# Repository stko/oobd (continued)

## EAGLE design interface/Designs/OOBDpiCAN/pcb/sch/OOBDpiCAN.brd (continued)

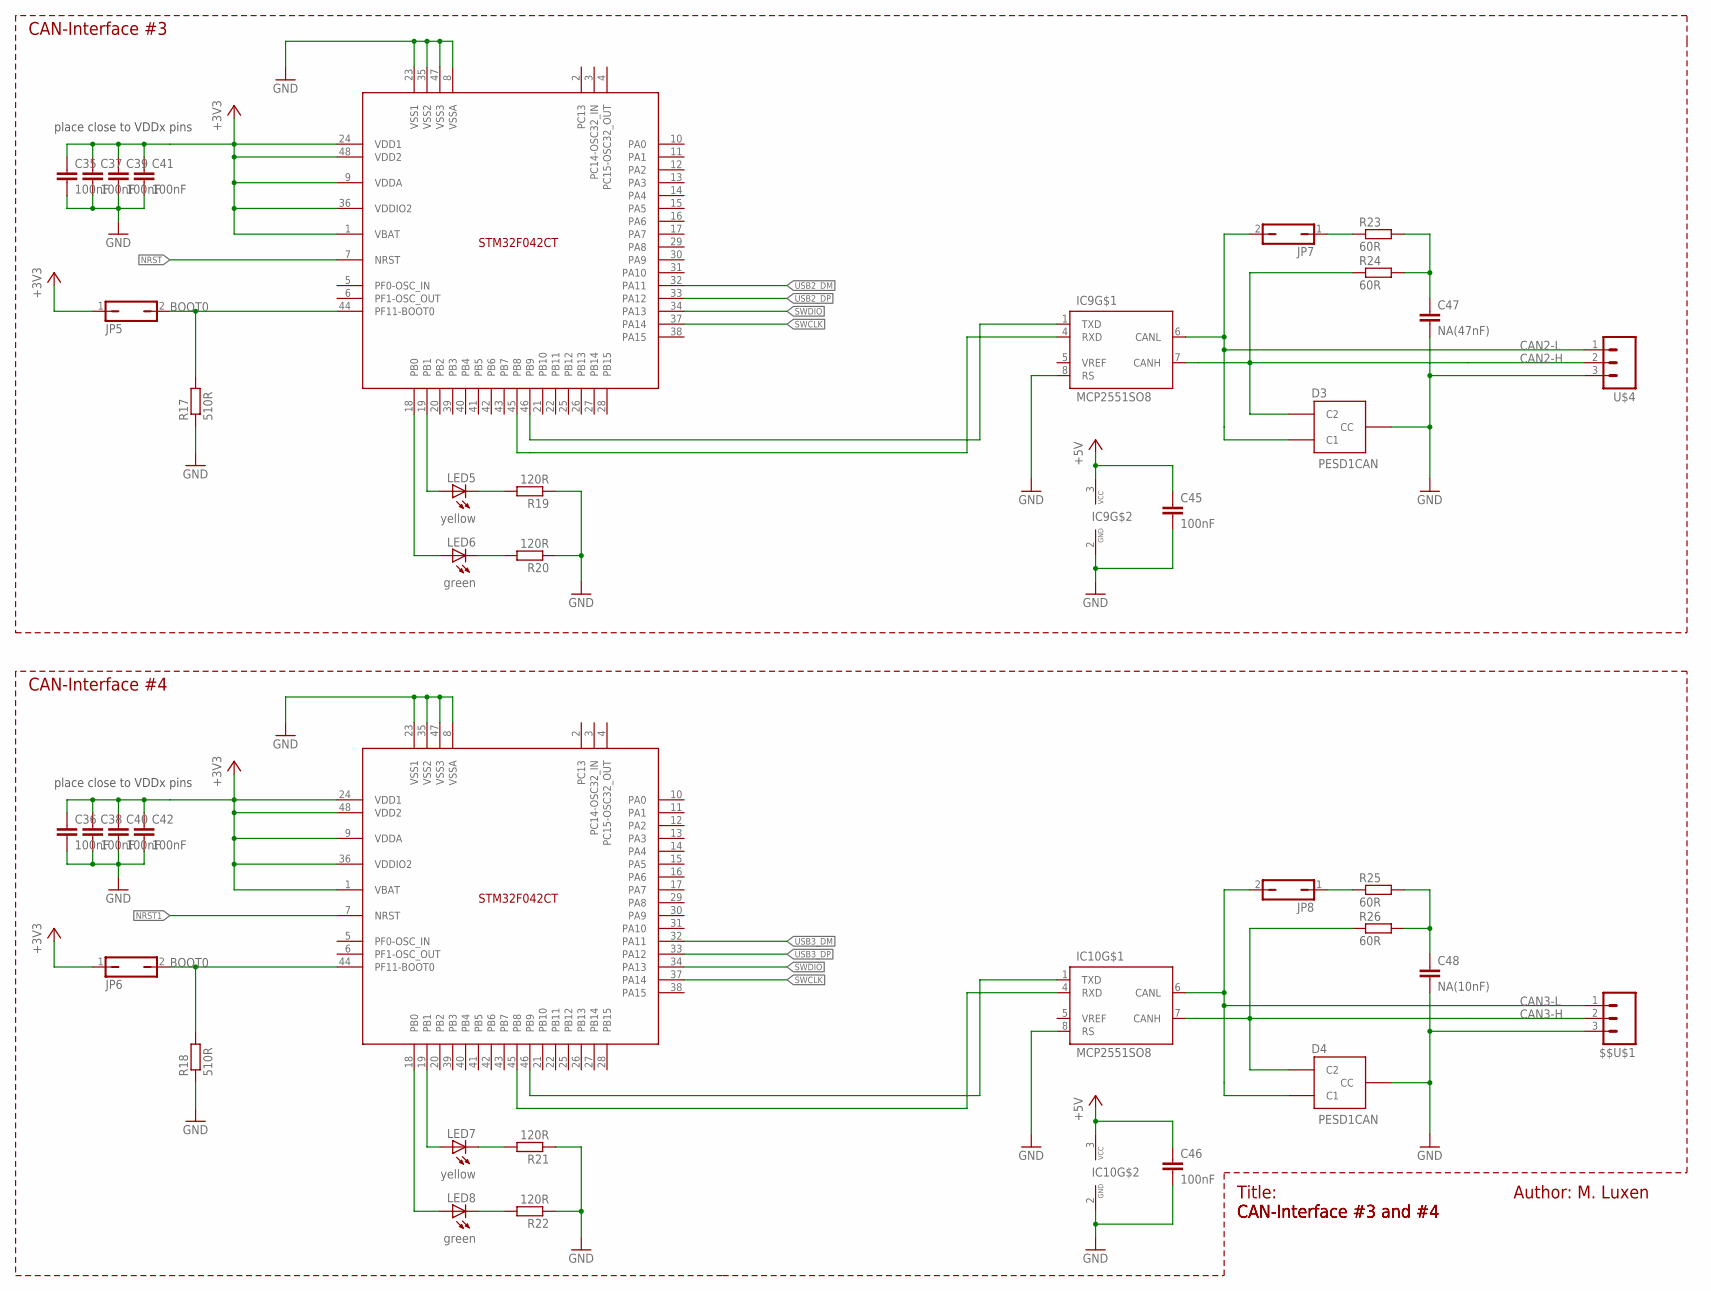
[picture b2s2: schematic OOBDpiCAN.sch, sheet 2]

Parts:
$$U$1: M03; SCREWTERMINAL-3.5MM-3
C35, C36, C37, C38, C39, C40, C41, C42, C45, C46: 100nF; C0603
C47: NA(47nF); C0603
C48: NA(10nF); C0603
D3, D4: PESD1CAN; SOT23
IC7, IC8: STM32F042CT; LQFP48
IC9, IC10: MCP2551SO8; SO08
JP5, JP6, JP7, JP8: JP1Q; JP1
LED5, LED7: yellow; CHIPLED_0805
LED6, LED8: green; CHIPLED_0805
R17, R18: 510R; R0603
R19, R20, R21, R22: 120R; R0603
R23, R24, R25, R26: 60R; R0603
U$4: M03; SCREWTERMINAL-3.5MM-3

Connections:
+3V3: C35.1, C36.1, C37.1, C38.1, C39.1, C40.1, C41.1, C42.1, IC7.1 (VBAT), IC7.9 (VDDA), IC7.24 (VDD1), IC7.36 (VDDIO2), IC7.48 (VDD2), IC8.1 (VBAT), IC8.9 (VDDA), IC8.24 (VDD1), IC8.36 (VDDIO2), IC8.48 (VDD2), JP5.1, JP6.1; also elsewhere on the board
+5V: C45.1, C46.1, IC9.3 (VCC), IC10.3 (VCC); also elsewhere on the board
BOOT0: IC7.44 (PF11-BOOT0), IC8.44 (PF11-BOOT0), JP5.2, JP6.2, R17.2, R18.2; also elsewhere on the board
CAN2-H: D3.2 (C2), IC9.7 (CANH), R24.1, U$4.2 (3)
CAN2-L: D3.1 (C1), IC9.6 (CANL), JP7.2, U$4.1 (2)
CAN3-H: $$U$1.2 (3), D4.2 (C2), IC10.7 (CANH), R26.1
CAN3-L: $$U$1.1 (2), D4.1 (C1), IC10.6 (CANL), JP8.2
GND: $$U$1.3 (4), C35.2, C36.2, C37.2, C38.2, C39.2, C40.2, C41.2, C42.2, C45.2, C46.2, C47.2, C48.2, D3.3 (CC), D4.3 (CC), IC7.8 (VSSA), IC7.23 (VSS1), IC7.35 (VSS2), IC7.47 (VSS3), IC8.8 (VSSA), IC8.23 (VSS1), IC8.35 (VSS2), IC8.47 (VSS3), IC9.2 (GND), IC9.8 (RS), IC10.2 (GND), IC10.8 (RS), R17.1, R18.1, R19.1, R20.1, R21.1, R22.1, U$4.3 (4); also elsewhere on the board
unnamed: IC7.19 (PB1), LED5.A
unnamed: JP7.1, R23.1
unnamed: IC7.18 (PB0), LED6.A
unnamed: LED5.C, R19.2
unnamed: LED6.C, R20.2
unnamed: IC8.19 (PB1), LED7.A
unnamed: IC8.18 (PB0), LED8.A
unnamed: LED7.C, R21.2
unnamed: LED8.C, R22.2
unnamed: C47.1, R23.2, R24.2
unnamed: IC8.45 (PB8), IC10.4 (RXD)
unnamed: IC8.46 (PB9), IC10.1 (TXD)
unnamed: IC7.45 (PB8), IC9.4 (RXD)
unnamed: IC7.46 (PB9), IC9.1 (TXD)
unnamed: JP8.1, R25.1
unnamed: C48.1, R25.2, R26.2
NRST: IC7.7 (NRST); also elsewhere on the board
NRST1: IC8.7 (NRST)
SWCLK: IC7.37 (PA14), IC8.37 (PA14); also elsewhere on the board
SWDIO: IC7.34 (PA13), IC8.34 (PA13); also elsewhere on the board
USB2_DM: IC7.32 (PA11); also elsewhere on the board
USB2_DP: IC7.33 (PA12); also elsewhere on the board
USB3_DM: IC8.32 (PA11); also elsewhere on the board
USB3_DP: IC8.33 (PA12); also elsewhere on the board

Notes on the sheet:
place close to VDDx pins
Author: M. Luxen
Title:
CAN-Interface #3 and #4
CAN-Interface #4
CAN-Interface #3

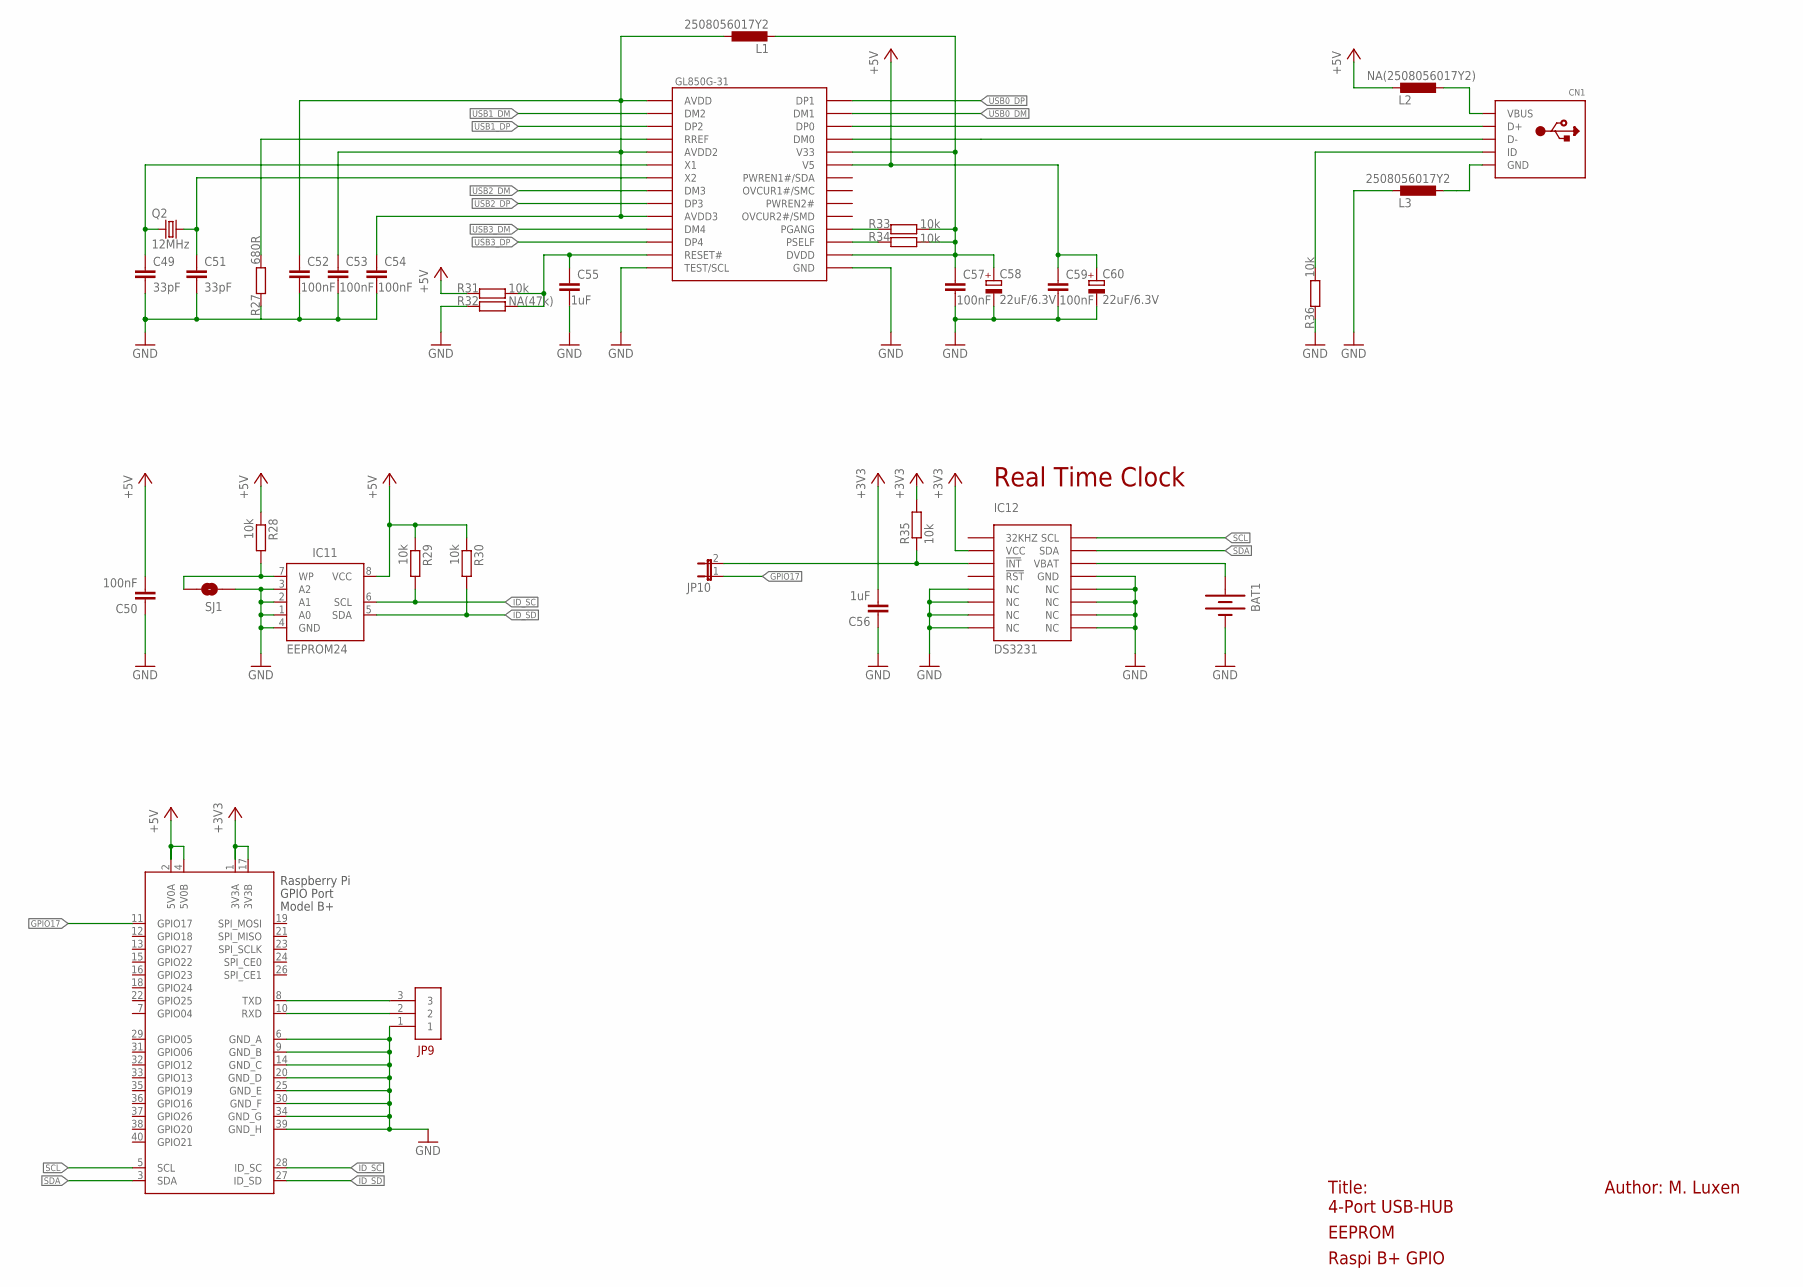
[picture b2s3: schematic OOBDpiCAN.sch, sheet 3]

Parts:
BAT1: BATTERY12PTH; BATTCON_12MM_PTH
C49, C51: 33pF; C0603
C50, C52, C53, C54, C57, C59: 100nF; C0603
C55, C56: 1uF; C0603
C58, C60: 22uF/6.3V; SMC_A
CN1: USBMOLEX; USB-MINIB-THM-MOLEX
IC11: EEPROM24; SOIC8
IC12: DS3231; SOIC-16W
JP9: MA03-1
JP10: JUMPER-2SMD-NO; SJ_2S-NO
L1, L3: 2508056017Y2; L0805
L2: NA(2508056017Y2); L0805
Q2: 12MHz; SM49
R27: 680R; R0603
R28, R29, R30, R31, R33, R34, R35, R36: 10k; R0603
R32: NA(47k); R0603
RPI1: RASPBERRY_HATHAT; CONNECTOR_B+_SMT_HAT
SJ1: SOLDERJUMPERTRACE; SJ_2S-TRACE
U$5: GL850G-31; TSSOP28

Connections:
+3V3: C56.2, IC12.2 (VCC), R35.2, RPI1.1 (3V3A), RPI1.17 (3V3B); also elsewhere on the board
+5V: C50.2, C59.1, C60.+, IC11.8 (VCC), L2.1, R28.1, R29.1, R30.1, R31.1, RPI1.2 (5V0A), RPI1.4 (5V0B), U$5.23 (V5); also elsewhere on the board
GND: BAT1.GND (-), C49.2, C50.1, C51.2, C52.2, C53.2, C54.2, C55.2, C56.1, C57.2, C58.-, C59.2, C60.-, IC11.1 (A0), IC11.2 (A1), IC11.3 (A2), IC11.4 (GND), IC12.5 (NC), IC12.6 (NC), IC12.7 (NC), IC12.8 (NC), IC12.9 (NC), IC12.10 (NC), IC12.11 (NC), IC12.12 (NC), IC12.13 (GND), JP9.1, L3.1, R27.1, R32.1, R36.1, RPI1.6 (GND_A), RPI1.9 (GND_B), RPI1.14 (GND_C), RPI1.20 (GND_D), RPI1.25 (GND_E), RPI1.30 (GND_F), RPI1.34 (GND_G), RPI1.39 (GND_H), SJ1.1, U$5.14 (TEST/SCL), U$5.15 (GND); also elsewhere on the board
GPIO17: JP10.1, RPI1.11 (GPIO17)
ID_SC: IC11.6 (SCL), R29.2, RPI1.28 (ID_SC)
ID_SD: IC11.5 (SDA), R30.2, RPI1.27 (ID_SD)
INT-: IC12.3 (!INT), JP10.2, R35.1
unnamed: C51.1, Q2.2, U$5.7 (X2)
unnamed: C49.1, Q2.1, U$5.6 (X1)
unnamed: IC11.7 (WP), R28.2, SJ1.2
unnamed: C57.1, C58.+, L1.2, R33.2, R34.2, U$5.16 (DVDD), U$5.24 (V33)
unnamed: R33.1, U$5.18 (PGANG)
unnamed: R34.1, U$5.17 (PSELF)
unnamed: C55.1, R31.2, R32.2, U$5.13 (RESET#)
unnamed: CN1.D+, U$5.26 (DP0)
unnamed: CN1.D-, U$5.25 (DM0)
unnamed: C52.1, C53.1, C54.1, L1.1, U$5.1 (AVDD), U$5.5 (AVDD2), U$5.10 (AVDD3)
unnamed: R27.2, U$5.4 (RREF)
unnamed: CN1.GND, L3.2
unnamed: CN1.VBUS, L2.2
unnamed: CN1.ID, R36.2
RXD: JP9.2, RPI1.10 (RXD)
SCL: IC12.16 (SCL), RPI1.5 (SCL)
SDA: IC12.15 (SDA), RPI1.3 (SDA)
TXD: JP9.3, RPI1.8 (TXD)
USB0_DM: U$5.27 (DM1); also elsewhere on the board
USB0_DP: U$5.28 (DP1); also elsewhere on the board
USB1_DM: U$5.2 (DM2); also elsewhere on the board
USB1_DP: U$5.3 (DP2); also elsewhere on the board
USB2_DM: U$5.8 (DM3); also elsewhere on the board
USB2_DP: U$5.9 (DP3); also elsewhere on the board
USB3_DM: U$5.11 (DM4); also elsewhere on the board
USB3_DP: U$5.12 (DP4); also elsewhere on the board
VBAT: BAT1.VCC@1 (+), IC12.14 (VBAT)

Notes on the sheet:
Author: M. Luxen
Title:
4-Port USB-HUB
Real Time Clock
EEPROM
Raspi B+ GPIO

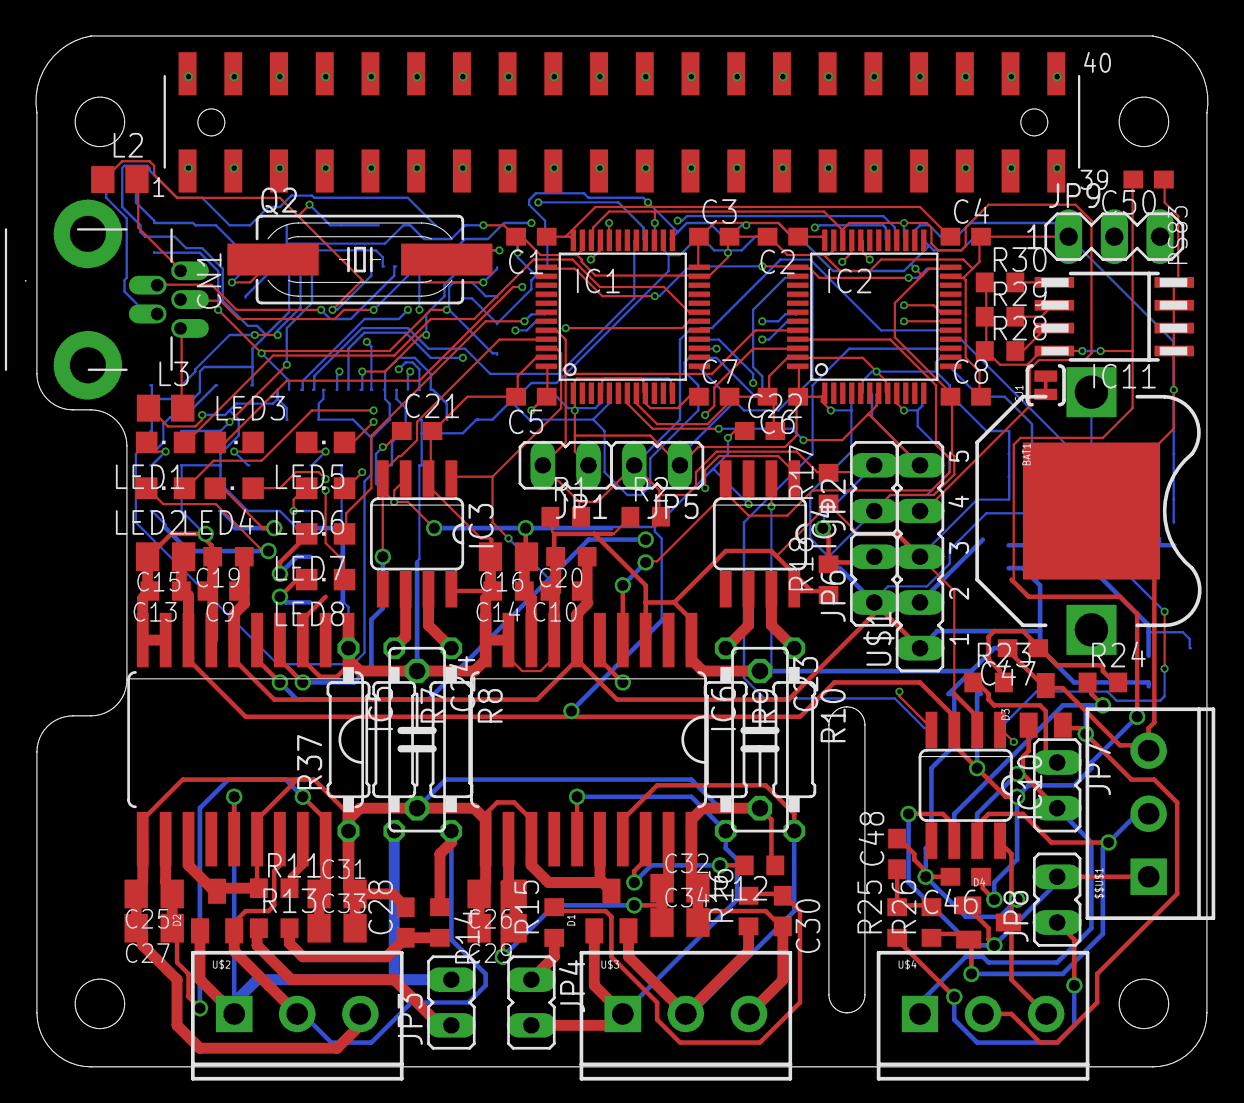
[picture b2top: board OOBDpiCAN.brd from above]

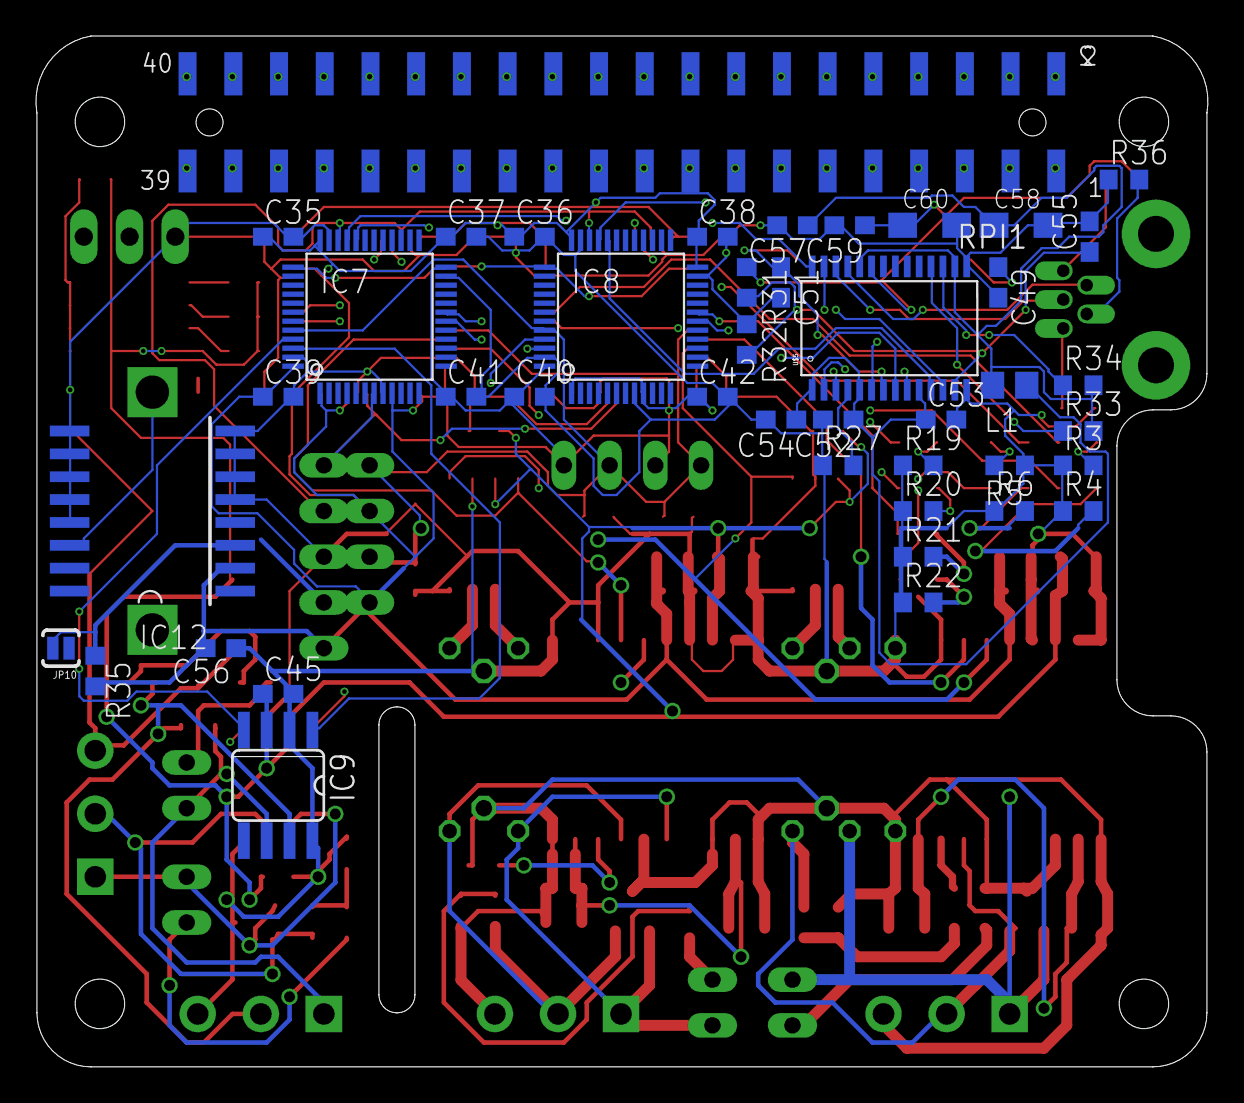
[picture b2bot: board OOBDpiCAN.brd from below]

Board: 4 copper layers, 65.1 x 57.3 mm, 139 parts (42 on the bottom side), 87 nets.

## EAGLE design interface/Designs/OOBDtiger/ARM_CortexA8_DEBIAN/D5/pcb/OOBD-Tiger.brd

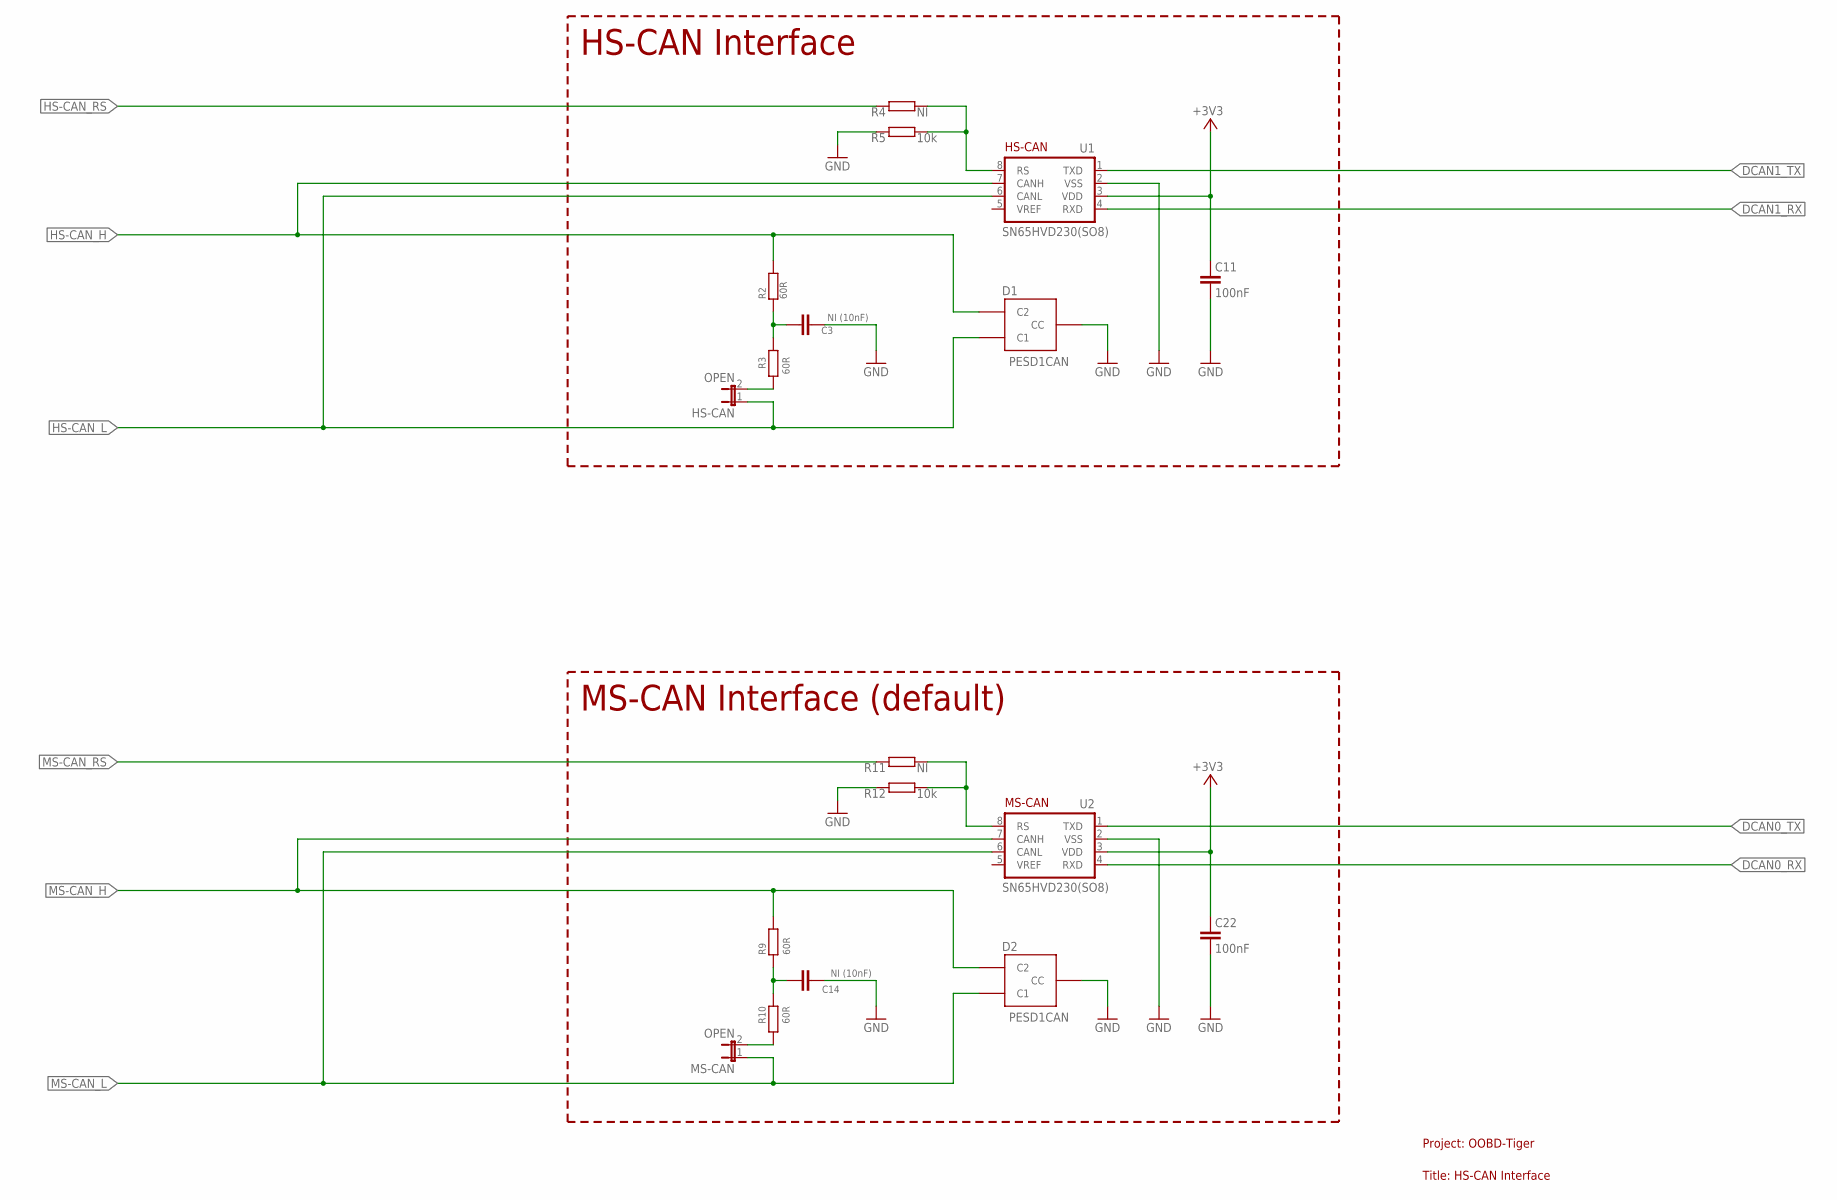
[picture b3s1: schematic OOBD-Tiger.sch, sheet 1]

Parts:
C3, C14: NI (10nF); C0603
C11, C22: 100nF; C0603K
D1, D2: PESD1CAN; SOT23
HS-CAN: OPEN; 1X02
MS-CAN: OPEN; 1X02
R2, R3, R9, R10: 60R; R0603
R4, R11: NI; R0603
R5, R12: 10k; R0603
U1, U2: SN65HVD230(SO8); SO-08

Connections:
DCAN0_RX: U2.4 (RXD); also elsewhere on the board
DCAN0_TX: U2.1 (TXD); also elsewhere on the board
DCAN1_RX: U1.4 (RXD); also elsewhere on the board
DCAN1_TX: U1.1 (TXD); also elsewhere on the board
GND: C3.2, C11.2, C14.2, C22.2, D1.3 (CC), D2.3 (CC), R5.2, R12.2, U1.2 (VSS), U2.2 (VSS); also elsewhere on the board
HS-CAN_H: D1.2 (C2), R2.2, U1.7 (CANH); also elsewhere on the board
HS-CAN_L: D1.1 (C1), HS-CAN.1, U1.6 (CANL); also elsewhere on the board
HS-CAN_RS: R4.2; also elsewhere on the board
MS-CAN_H: D2.2 (C2), R9.2, U2.7 (CANH); also elsewhere on the board
MS-CAN_L: D2.1 (C1), MS-CAN.1, U2.6 (CANL); also elsewhere on the board
MS-CAN_RS: R11.2; also elsewhere on the board
unnamed: C3.1, R2.1, R3.1
unnamed: R4.1, R5.1, U1.8 (RS)
unnamed: C14.1, R9.1, R10.1
unnamed: HS-CAN.2, R3.2
unnamed: MS-CAN.2, R10.2
unnamed: R11.1, R12.1, U2.8 (RS)

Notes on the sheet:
HS-CAN Interface
Project: OOBD-Tiger
Title: HS-CAN Interface
HS-CAN
MS-CAN Interface (default)
MS-CAN

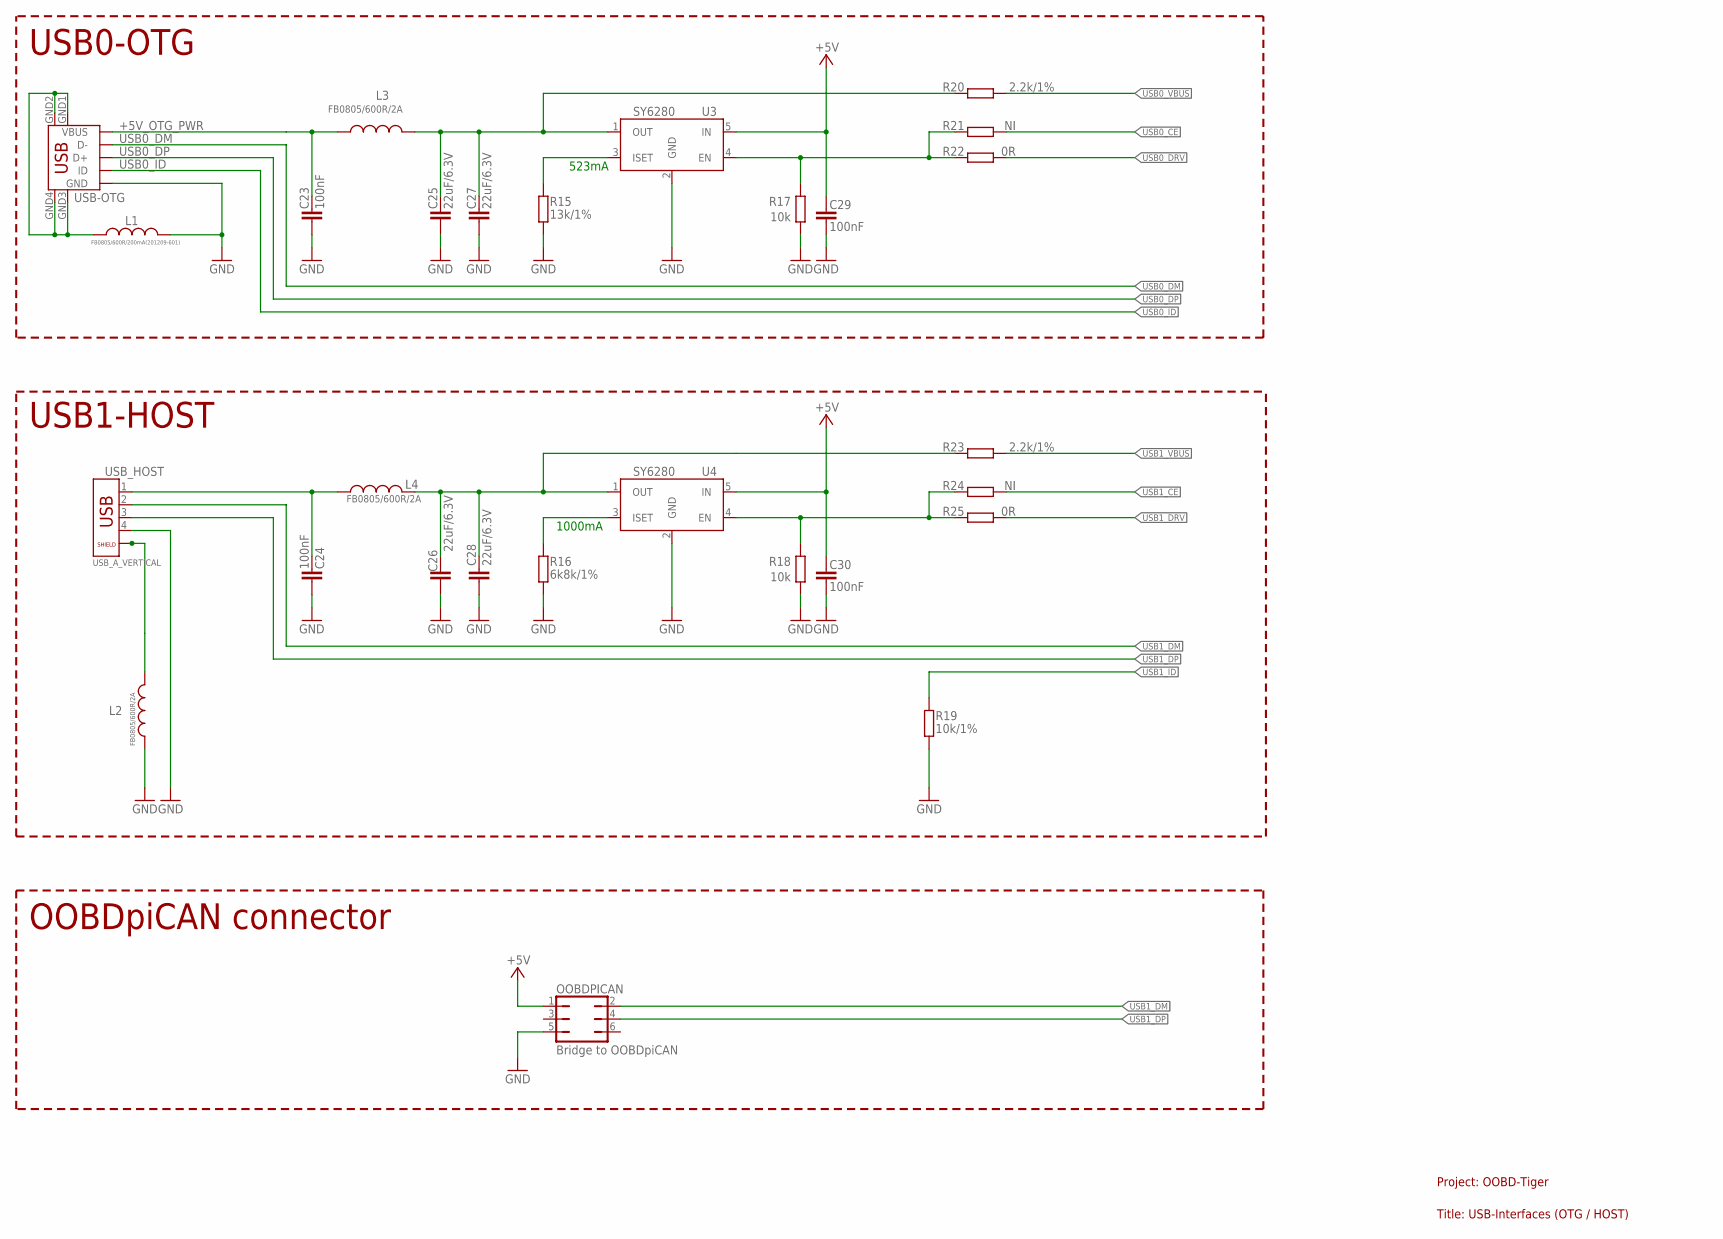
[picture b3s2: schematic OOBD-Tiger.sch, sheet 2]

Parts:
C23, C24, C29, C30: 100nF; C0603K
C25, C26, C27, C28: 22uF/6.3V; C0603
L1: FB0805/600R/200mA(201209-601); L0603
L2, L3, L4: FB0805/600R/2A; L0603
OOBDPICAN: Bridge to OOBDpiCAN; JP3Q
R15: 13k/1%; R0603
R16: 6k8k/1%; R0603
R17, R18: 10k; R0603
R19: 10k/1%; R0603
R20, R23: 2.2k/1%; R0603
R21, R24: NI; R0603
R22, R25: 0R; R0603
U3, U4: SY6280; SOT23-5
USB_HOST: USB_A_VERTICAL; USB_PN87520_DEV_PTH
USB_OTG: USB-OTG; USB_MINI_9PIN

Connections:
+5V: C29.1, C30.1, OOBDPICAN.1, U3.5 (IN), U4.5 (IN); also elsewhere on the board
+5V_OTG_PWR: C23.1, L3.1, USB_OTG.VBUS
GND: C23.2, C24.2, C25.2, C26.2, C27.2, C28.2, C29.2, C30.2, L1.1, L2.1, OOBDPICAN.5, R15.1, R16.1, R17.1, R18.1, R19.1, U3.2 (GND), U4.2 (GND), USB_HOST.4, USB_OTG.GND; also elsewhere on the board
unnamed: R16.2, U4.3 (ISET)
unnamed: C26.1, C28.1, L4.1, R23.2, U4.1 (OUT)
unnamed: C24.1, L4.2, USB_HOST.1
unnamed: L2.2, USB_HOST.P$1 (5), USB_HOST.P$2 (6)
unnamed: R15.2, U3.3 (ISET)
unnamed: C25.1, C27.1, L3.2, R20.2, U3.1 (OUT)
unnamed: L1.2, USB_OTG.GND1, USB_OTG.GND2, USB_OTG.GND3, USB_OTG.GND4
USB0_CE: R21.2; also elsewhere on the board
USB0_DM: USB_OTG.D-; also elsewhere on the board
USB0_DP: USB_OTG.D+; also elsewhere on the board
USB0_DRV: R22.2; also elsewhere on the board
USB0_EN: R17.2, R21.1, R22.1, U3.4 (EN)
USB0_ID: USB_OTG.ID; also elsewhere on the board
USB0_VBUS: R20.1; also elsewhere on the board
USB1_CE: R24.2; also elsewhere on the board
USB1_DM: OOBDPICAN.2, USB_HOST.2; also elsewhere on the board
USB1_DP: OOBDPICAN.4, USB_HOST.3; also elsewhere on the board
USB1_DRV: R25.2; also elsewhere on the board
USB1_EN: R18.2, R24.1, R25.1, U4.4 (EN)
USB1_ID: R19.2; also elsewhere on the board
USB1_VBUS: R23.1; also elsewhere on the board

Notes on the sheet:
USB0-OTG
Project: OOBD-Tiger
Title: USB-Interfaces (OTG / HOST)
USB1-HOST
523mA
1000mA
OOBDpiCAN connector

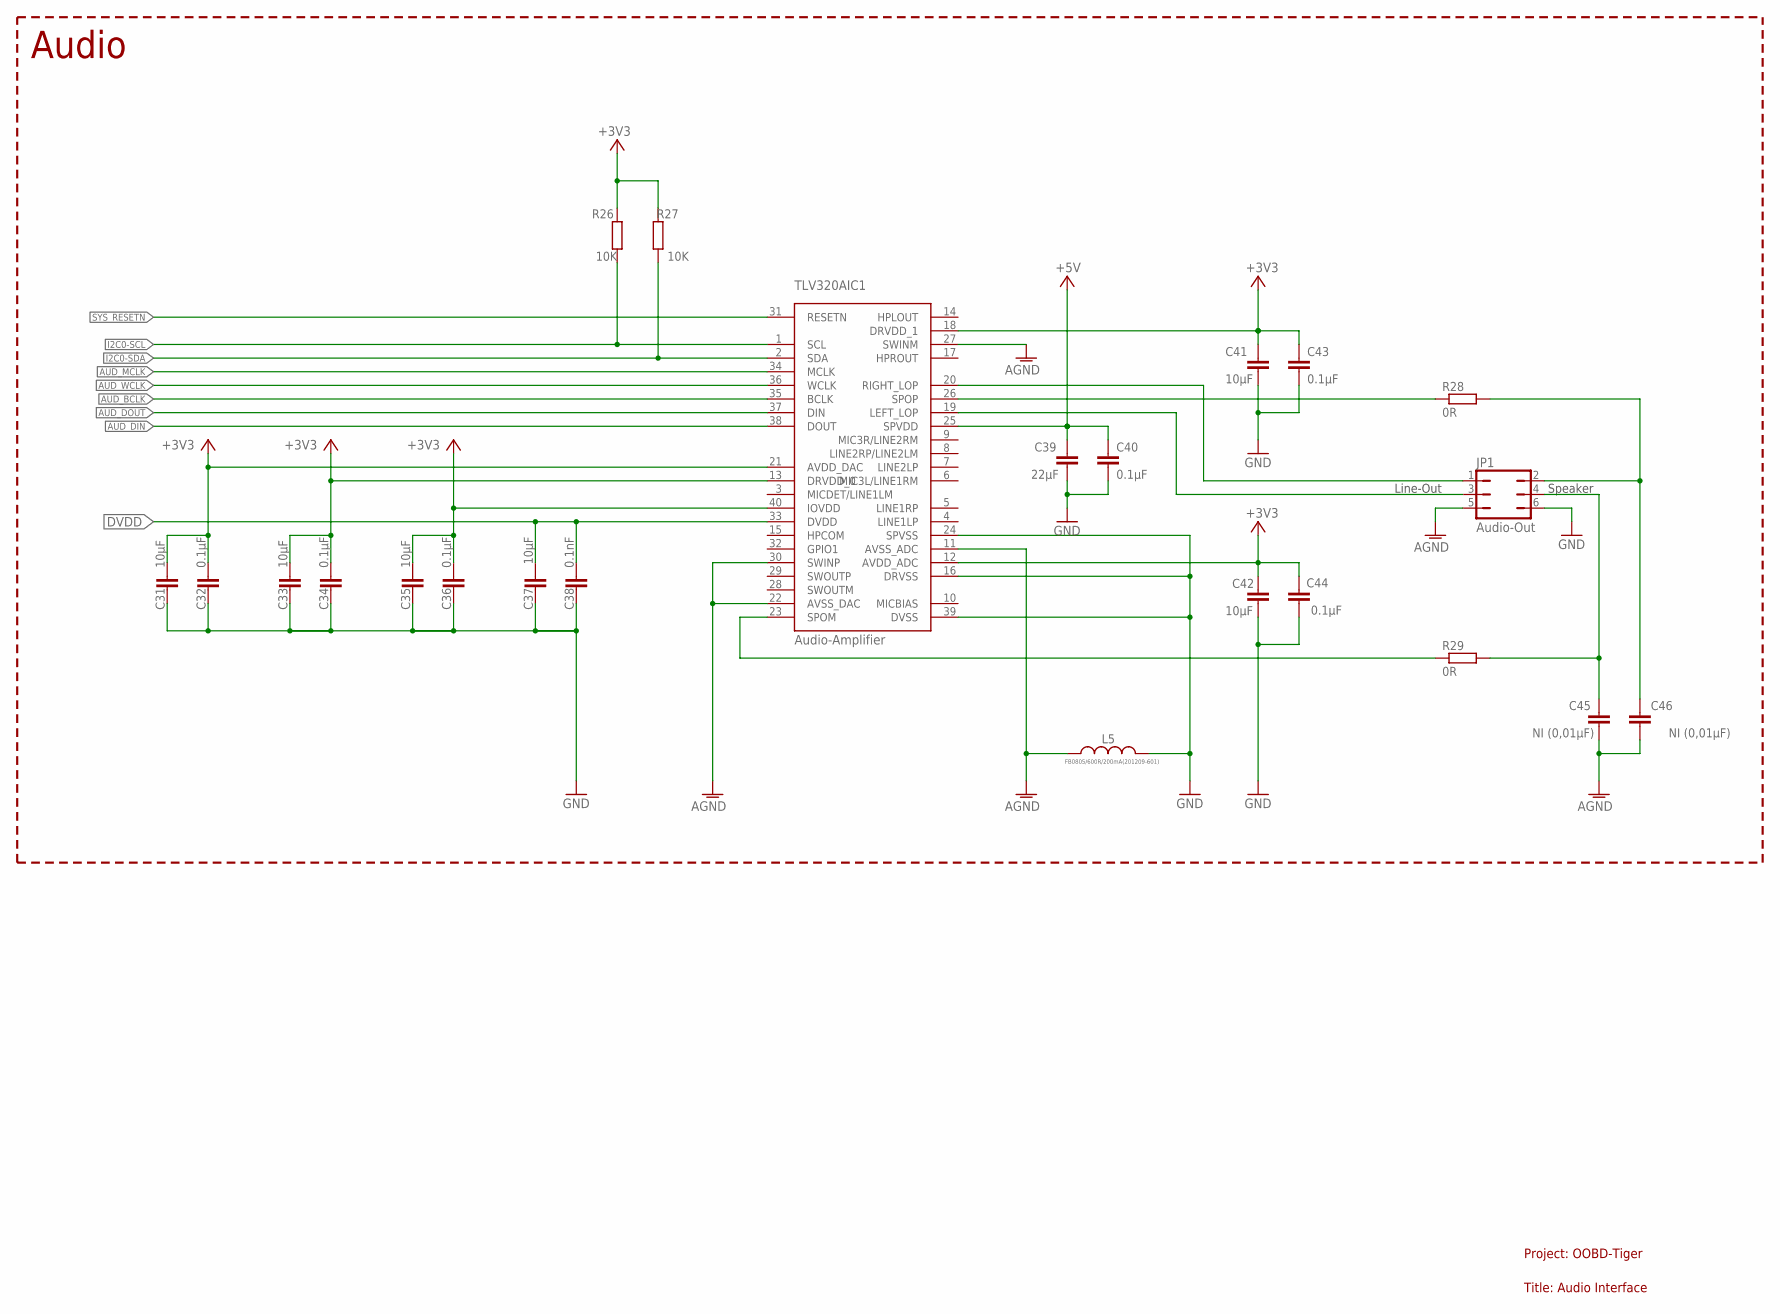
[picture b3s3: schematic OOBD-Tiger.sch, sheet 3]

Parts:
C31, C33, C35, C37, C41, C42: 10µF; 0603-CAP
C32, C34, C36, C40, C43, C44: 0.1µF; 0603-CAP
C38: 0.1nF; 0603-CAP
C39: 22µF; 0603-CAP
C45, C46: NI (0,01µF); 0603-CAP
JP1: Audio-Out; JP3Q
L5: FB0805/600R/200mA(201209-601); L0603
R26, R27: 10K; R0603
R28, R29: 0R; R0805
TLV320AIC1: Audio-Amplifier; QFN40-6X6

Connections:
+5V: C39.2, C40.2, TLV320AIC1.25 (SPVDD); also elsewhere on the board
AGND: C45.1, C46.1, JP1.5, L5.2, TLV320AIC1.11 (AVSS_ADC), TLV320AIC1.22 (AVSS_DAC), TLV320AIC1.27 (SWINM), TLV320AIC1.30 (SWINP)
AUD_BCLK: TLV320AIC1.35 (BCLK); also elsewhere on the board
AUD_DIN: TLV320AIC1.38 (DOUT); also elsewhere on the board
AUD_DOUT: TLV320AIC1.37 (DIN); also elsewhere on the board
AUD_MCLK: TLV320AIC1.34 (MCLK); also elsewhere on the board
AUD_WCLK: TLV320AIC1.36 (WCLK); also elsewhere on the board
DVDD: C37.2, C38.2, TLV320AIC1.33 (DVDD); also elsewhere on the board
GND: C31.1, C32.1, C33.1, C34.1, C35.1, C36.1, C37.1, C38.1, C39.1, C40.1, C41.2, C42.2, C43.2, C44.2, JP1.6, L5.1, TLV320AIC1.16 (DRVSS), TLV320AIC1.24 (SPVSS), TLV320AIC1.39 (DVSS); also elsewhere on the board
I2C0-SCL: R26.1, TLV320AIC1.1 (SCL); also elsewhere on the board
I2C0-SDA: R27.1, TLV320AIC1.2 (SDA); also elsewhere on the board
unnamed: JP1.1, TLV320AIC1.20 (RIGHT_LOP)
unnamed: C45.2, JP1.4, R29.2
unnamed: C46.2, JP1.2, R28.2
unnamed: R28.1, TLV320AIC1.26 (SPOP)
unnamed: R29.1, TLV320AIC1.23 (SPOM)
unnamed: JP1.3, TLV320AIC1.19 (LEFT_LOP)
SYS_RESETN: TLV320AIC1.31 (RESETN); also elsewhere on the board

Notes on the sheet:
Project: OOBD-Tiger
Title: Audio Interface
Audio
Line-Out
Speaker
